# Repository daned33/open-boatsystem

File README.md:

View this project on [CADLAB.io](https://cadlab.io/project/24280). 

# open-boatsystem
Project page for the open source/hardware project on building a "smart" boat electrical system.

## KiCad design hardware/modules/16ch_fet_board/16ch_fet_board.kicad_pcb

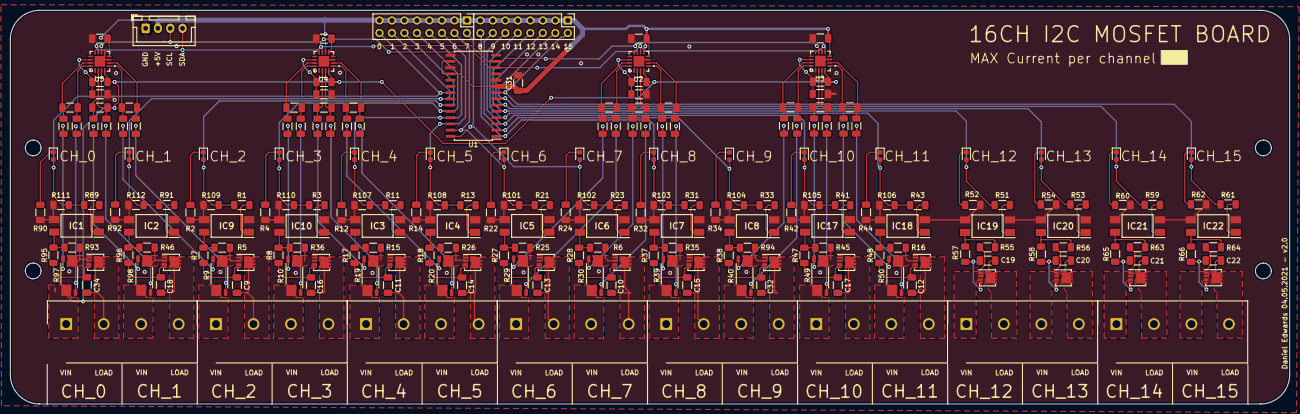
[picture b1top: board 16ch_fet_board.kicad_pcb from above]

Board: 2 copper layers, 260.0 x 80.0 mm, 217 parts (0 on the bottom side), 180 nets.

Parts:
C1, C2, C3, C5, C6, C7, C23, C24, C25, C27, C28, C29: Cf; C_1206_3216Metric_Pad1.33x1.80mm_HandSolder
C4, C8, C26, C30, C31: 0u1; C_1206_3216Metric_Pad1.33x1.80mm_HandSolder
C9, C10, C11, C12, C13, C14, C15, C16, C17, C18, C19, C20, C21, C22, C32, C34: 10nF; C_1206_3216Metric_Pad1.33x1.80mm_HandSolder
D1, D2, D3, D4, D5, D6, D7, D8, D9, D10, D11, D12, D13, D14, D17, D18: Or; LEDC1608X80N
IC1, IC2, IC3, IC4, IC5, IC6, IC7, IC8, IC9, IC10, IC17, IC18, IC19, IC20, IC21, IC22: LTV-816S-TA1; SOP254P1016X460-4N
J1: Conn_01x04_Female; JST_XH_B4B-XH-A_1x04_P2.50mm_Vertical
J2, J3, J4, J5, J6, J7, J8, J9: TB005-762-04BE; SHDR4W100P0X762_1X4_3048X1260X2170P
Q1, Q2, Q3, Q4, Q5, Q6, Q7, Q8, Q9, Q10, Q11, Q12, Q13, Q14, Q15, Q16: SiSS63DN; Vishay_PowerPAK_1212-8_Single
R1, R3, R11, R13, R21, R23, R31, R33, R41, R43, R51, R53, R59, R61, R89, R91, R101, R102, R103, R104, R105, R106, R107, R108, R109, R110, R111, R112: 1.2K; R_1206_3216Metric_Pad1.30x1.75mm_HandSolder
R2, R4, R12, R14, R22, R24, R32, R34, R42, R44, R90, R92: 1k; R_1206_3216Metric_Pad1.30x1.75mm_HandSolder
R5, R6, R15, R16, R25, R26, R35, R36, R45, R46, R55, R56, R63, R64, R93, R94: 10K; R_1206_3216Metric_Pad1.30x1.75mm_HandSolder
R7, R8, R17, R18, R27, R28, R37, R38, R47, R48, R57, R58, R65, R66, R95, R96: 100; R_1206_3216Metric_Pad1.30x1.75mm_HandSolder
R9, R10, R19, R20, R29, R30, R39, R40, R49, R50, R97, R98: 1m; R_Shunt_Vishay_WSK2512_6332Metric_T1.19mm
R52, R54, R60, R62: 1K; R_1206_3216Metric_Pad1.30x1.75mm_HandSolder
R67, R68, R69, R70, R71, R72, R73, R74, R75, R76, R77, R78, R79, R80, R81, R82, R83, R84, R85, R86, R87, R88, R99, R100: Rf; R_1206_3216Metric_Pad1.30x1.75mm_HandSolder
Rdiv: Rdiv; R_1206_3216Metric_Pad1.30x1.75mm_HandSolder
Rdiv#2, Rdiv#3, Rdiv#4: Rdiv; R_1206_3216Metric_Pad1.30x1.75mm_HandSolder
Rpu: R_Small; R_1206_3216Metric_Pad1.30x1.75mm_HandSolder
Rpu#2, Rpu#3, Rpu#4: R_Small; R_1206_3216Metric_Pad1.30x1.75mm_HandSolder
SW1, SW2: SW_DIP_x08; PinHeader_2x08_P2.54mm_Vertical
U1: MCP23017_SO; SOIC-28W_7.5x17.9mm_P1.27mm
U2, U3, U4, U5: INA3221AIRGVR; QFN65P400X400X100-17N

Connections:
+5V: C4.1, C8.1, C26.1, C30.1, C31.1, J1.2, SW1.1, SW1.2, SW1.3, SW1.4, SW1.5, SW1.6, SW1.7, SW1.8, SW2.1, SW2.2, SW2.3, SW2.4, SW2.5, SW2.6, SW2.7, SW2.8, U1.9, U1.16, U1.18, U2.4, U3.4, U4.4, U4.5, U5.4
/+12V: J2.1, R97.4, Rpu.1, Rpu#2.1, Rpu#3.1, Rpu#4.1, U2.16, U3.16, U4.16, U5.16
/FET_0: D17.2, R89.2, R111.1, SW1.16, U1.21
/FET_0-1/IN_B: J2.3, R98.4
/FET_0-1/OUT_A: C34.1, J2.2, Q13.5
/FET_0-1/OUT_B: C18.1, J2.4, Q14.5
/FET_1: D18.2, R91.2, R112.1, SW1.15, U1.22
/FET_2: D1.2, R1.2, R109.1, SW1.14, U1.23
/FET_2-3/IN_A: J3.1, R9.4
/FET_2-3/IN_B: J3.3, R10.4
/FET_2-3/OUT_A: C9.1, J3.2, Q11.5
/FET_2-3/OUT_B: C16.1, J3.4, Q12.5
/FET_3: D2.2, R3.2, R110.1, SW1.13, U1.24
/FET_4: D3.2, R11.2, R107.1, SW1.12, U1.25
/FET_4-5/IN_A: J4.1, R19.4
/FET_4-5/IN_B: J4.3, R20.4
/FET_4-5/OUT_A: C11.1, J4.2, Q9.5
/FET_4-5/OUT_B: C14.1, J4.4, Q10.5
/FET_5: D4.2, R13.2, R108.1, SW1.11, U1.26
/FET_6: D5.2, R21.2, R101.1, SW1.10, U1.27
/FET_6-7/IN_A: J5.1, R29.4
/FET_6-7/IN_B: J5.3, R30.4
/FET_6-7/OUT_A: C13.1, J5.2, Q1.5
/FET_6-7/OUT_B: C10.1, J5.4, Q2.5
/FET_7: D6.2, R23.2, R102.1, SW1.9, U1.28
/FET_8: D7.2, R31.2, R103.1, SW2.16, U1.1
/FET_8-9/IN_A: J6.1, R39.4
/FET_8-9/IN_B: J6.3, R40.4
/FET_8-9/OUT_A: C15.1, J6.2, Q15.5
/FET_8-9/OUT_B: C32.1, J6.4, Q16.5
/FET_9: D8.2, R33.2, R104.1, SW2.15, U1.2
/FET_10: D9.2, R41.2, R105.1, SW2.14, U1.3
/FET_10-11/IN_A: J7.1, R49.4
/FET_10-11/IN_B: J7.3, R50.4
/FET_10-11/OUT_A: C17.1, J7.2, Q3.5
/FET_10-11/OUT_B: C12.1, J7.4, Q4.5
/FET_11: D10.2, R43.2, R106.1, SW2.13, U1.4
/FET_12: D11.2, R51.2, SW2.12, U1.5
/FET_12-13/IN_A: J8.1, Q5.1, Q5.2, Q5.3, R55.1
/FET_12-13/IN_B: J8.3, Q6.1, Q6.2, Q6.3, R56.1
/FET_12-13/OUT_A: C19.1, J8.2, Q5.5
/FET_12-13/OUT_B: C20.1, J8.4, Q6.5
/FET_13: D12.2, R53.2, SW2.11, U1.6
/FET_14: D13.2, R59.2, SW2.10, U1.7
/FET_14-15/IN_A: J9.1, Q7.1, Q7.2, Q7.3, R63.1
/FET_14-15/IN_B: J9.3, Q8.1, Q8.2, Q8.3, R64.1
/FET_14-15/OUT_A: C21.1, J9.2, Q7.5
/FET_14-15/OUT_B: C22.1, J9.4, Q8.5
/FET_15: D14.2, R61.2, SW2.9, U1.8
/INA_0/PV: Rdiv.1, Rpu.2, U5.10
/INA_1/PV: Rdiv#2.1, Rpu#2.2, U4.10
/INA_2/PV: Rdiv#4.1, Rpu#4.2, U2.10
/INA_3/PV: Rdiv#3.1, Rpu#3.2, U3.10
/SCL: J1.3, U1.12, U2.6, U3.5, U3.6, U4.6, U5.6
/SDA: J1.4, U1.13, U2.5, U2.7, U3.7, U4.7, U5.7
/SR_0+: R97.3, R99.1
/SR_0-: R97.2, R100.1
/SR_1+: R87.1, R98.3
/SR_1-: R88.1, R98.2
/SR_2+: R9.3, R85.1
/SR_2-: R9.2, R86.1
/SR_3+: R10.3, R83.1
/SR_3-: R10.2, R84.1
/SR_4+: R19.3, R81.1
/SR_4-: R19.2, R82.1
/SR_5+: R20.3, R79.1
/SR_5-: R20.2, R80.1
/SR_6+: R29.3, R71.1
/SR_6-: R29.2, R72.1
/SR_7+: R30.3, R69.1
/SR_7-: R30.2, R70.1
/SR_8+: R39.3, R67.1
/SR_8-: R39.2, R68.1
/SR_9+: R40.3, R77.1
/SR_9-: R40.2, R78.1
/SR_10+: R49.3, R75.1
/SR_10-: R49.2, R76.1
/SR_11+: R50.3, R73.1
/SR_11-: R50.2, R74.1
GND: C4.2, C8.2, C26.2, C30.2, C31.2, IC1.2, IC1.3, IC2.2, IC2.3, IC3.2, IC3.3, IC4.2, IC4.3, IC5.2, IC5.3, IC6.2, IC6.3, IC7.2, IC7.3, IC8.2, IC8.3, IC9.2, IC9.3, IC10.2, IC10.3, IC17.2, IC17.3, IC18.2, IC18.3, IC19.2, IC19.3, IC20.2, IC20.3, IC21.2, IC21.3, IC22.2, IC22.3, J1.1, R2.1, R4.1, R12.1, R14.1, R22.1, R24.1, R32.1, R34.1, R42.1, R44.1, R52.1, R54.1, R60.1, R62.1, R90.1, R92.1, R101.2, R102.2, R103.2, R104.2, R105.2, R106.2, R107.2, R108.2, R109.2, R110.2, R111.2, R112.2, Rdiv.2, Rdiv#2.2, Rdiv#3.2, Rdiv#4.2, U1.10, U1.15, U1.17, U2.3, U2.17, U3.3, U3.17, U4.3, U4.17, U5.3, U5.5, U5.17
unnamed: C1.1, R67.2, U2.2
unnamed: C1.2, R68.2, U2.1
unnamed: C2.1, R69.2, U2.15
unnamed: C2.2, R70.2, U2.14
unnamed: C3.1, R71.2, U2.12
unnamed: C3.2, R72.2, U2.11
unnamed: C5.1, R73.2, U3.2
unnamed: C5.2, R74.2, U3.1
unnamed: C6.1, R75.2, U3.15
unnamed: C6.2, R76.2, U3.14
unnamed: C7.1, R77.2, U3.12
unnamed: C7.2, R78.2, U3.11
unnamed: C9.2, Q11.4, R7.1
unnamed: C10.2, Q2.4, R28.1
unnamed: C11.2, Q9.4, R17.1
unnamed: C12.2, Q4.4, R48.1
unnamed: C13.2, Q1.4, R27.1
unnamed: C14.2, Q10.4, R18.1
unnamed: C15.2, Q15.4, R37.1
unnamed: C16.2, Q12.4, R8.1
unnamed: C17.2, Q3.4, R47.1
unnamed: C18.2, Q14.4, R96.1
unnamed: C19.2, Q5.4, R57.1
unnamed: C20.2, Q6.4, R58.1
unnamed: C21.2, Q7.4, R65.1
unnamed: C22.2, Q8.4, R66.1
unnamed: C23.1, R79.2, U4.2
unnamed: C23.2, R80.2, U4.1
unnamed: C24.1, R81.2, U4.15
unnamed: C24.2, R82.2, U4.14
unnamed: C25.1, R83.2, U4.12
unnamed: C25.2, R84.2, U4.11
unnamed: C27.1, R85.2, U5.2
unnamed: C27.2, R86.2, U5.1
unnamed: C28.1, R87.2, U5.15
unnamed: C28.2, R88.2, U5.14
unnamed: C29.1, R99.2, U5.12
unnamed: C29.2, R100.2, U5.11
unnamed: C32.2, Q16.4, R38.1
unnamed: C34.2, Q13.4, R95.1
unnamed: D1.1, R2.2
unnamed: D2.1, R4.2
unnamed: D3.1, R12.2
unnamed: D4.1, R14.2
unnamed: D5.1, R22.2
unnamed: D6.1, R24.2
unnamed: D7.1, R32.2
unnamed: D8.1, R34.2
unnamed: D9.1, R42.2
unnamed: D10.1, R44.2
unnamed: D11.1, R52.2
unnamed: D12.1, R54.2
unnamed: D13.1, R60.2
unnamed: D14.1, R62.2
unnamed: D17.1, R90.2
unnamed: D18.1, R92.2
unnamed: IC1.1, R89.1
unnamed: IC1.4, R93.2, R95.2
unnamed: IC2.1, R91.1
unnamed: IC2.4, R46.2, R96.2
unnamed: IC3.1, R11.1
unnamed: IC3.4, R15.2, R17.2
unnamed: IC4.1, R13.1
unnamed: IC4.4, R18.2, R26.2
unnamed: IC5.1, R21.1
unnamed: IC5.4, R25.2, R27.2
unnamed: IC6.1, R23.1
unnamed: IC6.4, R6.2, R28.2
unnamed: IC7.1, R31.1
unnamed: IC7.4, R35.2, R37.2
unnamed: IC8.1, R33.1
unnamed: IC8.4, R38.2, R94.2
unnamed: IC9.1, R1.1
unnamed: IC9.4, R5.2, R7.2
unnamed: IC10.1, R3.1
unnamed: IC10.4, R8.2, R36.2
unnamed: IC17.1, R41.1
unnamed: IC17.4, R45.2, R47.2
unnamed: IC18.1, R43.1
unnamed: IC18.4, R16.2, R48.2
unnamed: IC19.1, R51.1
unnamed: IC19.4, R55.2, R57.2
unnamed: IC20.1, R53.1
unnamed: IC20.4, R56.2, R58.2
unnamed: IC21.1, R59.1
unnamed: IC21.4, R63.2, R65.2
unnamed: IC22.1, R61.1
unnamed: IC22.4, R64.2, R66.2
unnamed: Q1.1, Q1.2, Q1.3, R25.1, R29.1
unnamed: Q2.1, Q2.2, Q2.3, R6.1, R30.1
unnamed: Q3.1, Q3.2, Q3.3, R45.1, R49.1
unnamed: Q4.1, Q4.2, Q4.3, R16.1, R50.1
unnamed: Q9.1, Q9.2, Q9.3, R15.1, R19.1
unnamed: Q10.1, Q10.2, Q10.3, R20.1, R26.1
unnamed: Q11.1, Q11.2, Q11.3, R5.1, R9.1
unnamed: Q12.1, Q12.2, Q12.3, R10.1, R36.1
unnamed: Q13.1, Q13.2, Q13.3, R93.1, R97.1
unnamed: Q14.1, Q14.2, Q14.3, R46.1, R98.1
unnamed: Q15.1, Q15.2, Q15.3, R35.1, R39.1
unnamed: Q16.1, Q16.2, Q16.3, R40.1, R94.1

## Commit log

2021-05-09 16ch MOSFET board v2.0 initial upload
2021-05-09 Backlink to CADLAB.io has been added.
